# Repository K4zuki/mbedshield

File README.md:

# mbedshield
mbeDshield design and documents

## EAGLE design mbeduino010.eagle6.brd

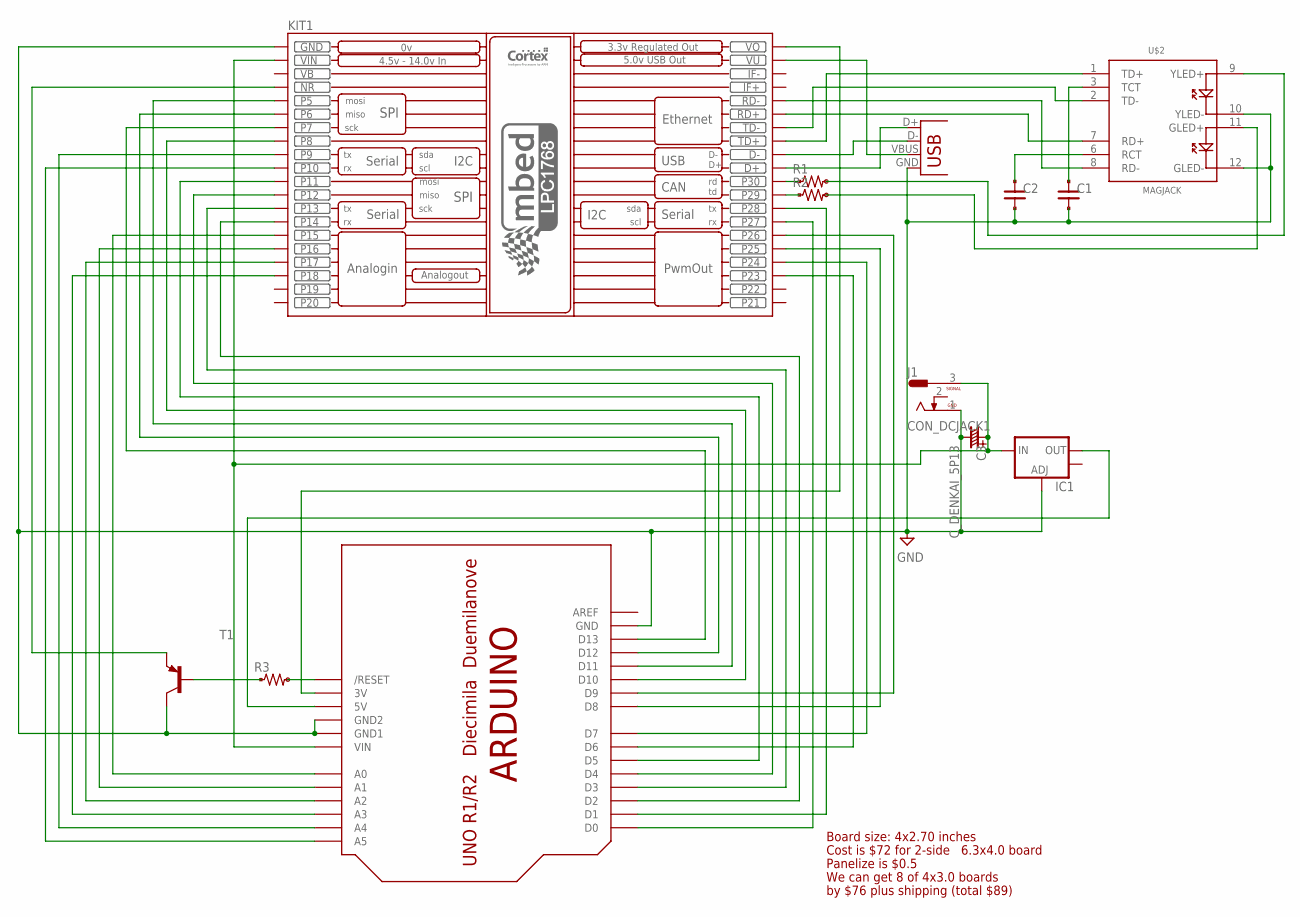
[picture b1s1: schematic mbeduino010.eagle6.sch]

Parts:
C1, C2: C_PAD_PAD_2125; CR_2125
C3: C_DENKAI_5P13; C_2.5PHI6
IC1: V_REG_LM1117SOT223; SOT223
J1: CON_DCJACK1; CON_DCJACK
KIT1: MBED_NXP_LPC1768; MBED-KIT
R1, R2, R3: R_US_PAD_VIA_2125; R_2125_PADVIA
T1: -PNP-SOT23-BCE; SOT23-BCE
U$1: ARDUINO-NOHOLE
U$2: MAGJACK
X1: USB-A-S

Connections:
GND: C1.2, C2.2, C3.-, IC1.1 (ADJ), J1.1 (3), KIT1.GND, T1.C, U$1.GND, U$1.GND1, U$1.GND2, U$2.10 (YLED-), U$2.12 (GLED-), X1.GND
unnamed: KIT1.NR, T1.E
unnamed: C3.+, IC1.3 (IN), J1.3 (1), KIT1.VIN, U$1.VIN
unnamed: KIT1.VOUT (VO), U$1.3V
unnamed: KIT1.P$15 (P15), U$1.A0
unnamed: KIT1.P$16 (P16), U$1.A1
unnamed: KIT1.P$17 (P17), U$1.A2
unnamed: KIT1.P$18 (P18), U$1.A3
unnamed: KIT1.P$9 (P9), U$1.A4
unnamed: KIT1.P$10 (P10), U$1.A5
unnamed: KIT1.P$27 (P27), U$1.D0
unnamed: KIT1.P$28 (P28), U$1.D1
unnamed: KIT1.P$14 (P14), U$1.D2
unnamed: KIT1.P$13 (P13), U$1.D3
unnamed: KIT1.P$12 (P12), U$1.D4
unnamed: KIT1.P$11 (P11), U$1.D5
unnamed: KIT1.P$23 (P23), U$1.D6
unnamed: KIT1.P$24 (P24), U$1.D7
unnamed: KIT1.P$25 (P25), U$1.D8
unnamed: KIT1.P$26 (P26), U$1.D9
unnamed: KIT1.P$8 (P8), U$1.D10
unnamed: KIT1.P$5 (P5), U$1.D11
unnamed: KIT1.P$6 (P6), U$1.D12
unnamed: KIT1.P$7 (P7), U$1.D13
unnamed: KIT1.D-, X1.D-
unnamed: KIT1.D+, X1.D+
unnamed: KIT1.VU, X1.VBUS
unnamed: R3.PAD, T1.B
unnamed: R3.VIA, U$1.RESET (/RESET)
unnamed: C1.1, U$2.3 (TCT)
unnamed: C2.1, U$2.6 (RCT)
unnamed: KIT1.RD+, U$2.7 (RD+)
unnamed: KIT1.RD-, U$2.8 (RD-)
unnamed: KIT1.TD-, U$2.2 (TD-)
unnamed: KIT1.TD+, U$2.1 (TD+)
unnamed: IC1.2 (OUT), U$1.5V
unnamed: KIT1.P$30 (P30), R1.PAD
unnamed: KIT1.P$29 (P29), R2.PAD
unnamed: R1.VIA, U$2.9 (YLED+)
unnamed: R2.VIA, U$2.11 (GLED+)
VB: KIT1.VB

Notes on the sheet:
Board size: 4x2.70 inches
Cost is $72 for 2-side
6.3x4.0 board
Panelize is $0.5
We can get 8 of 4x3.0 boards
by $76 plus shipping (total $89)

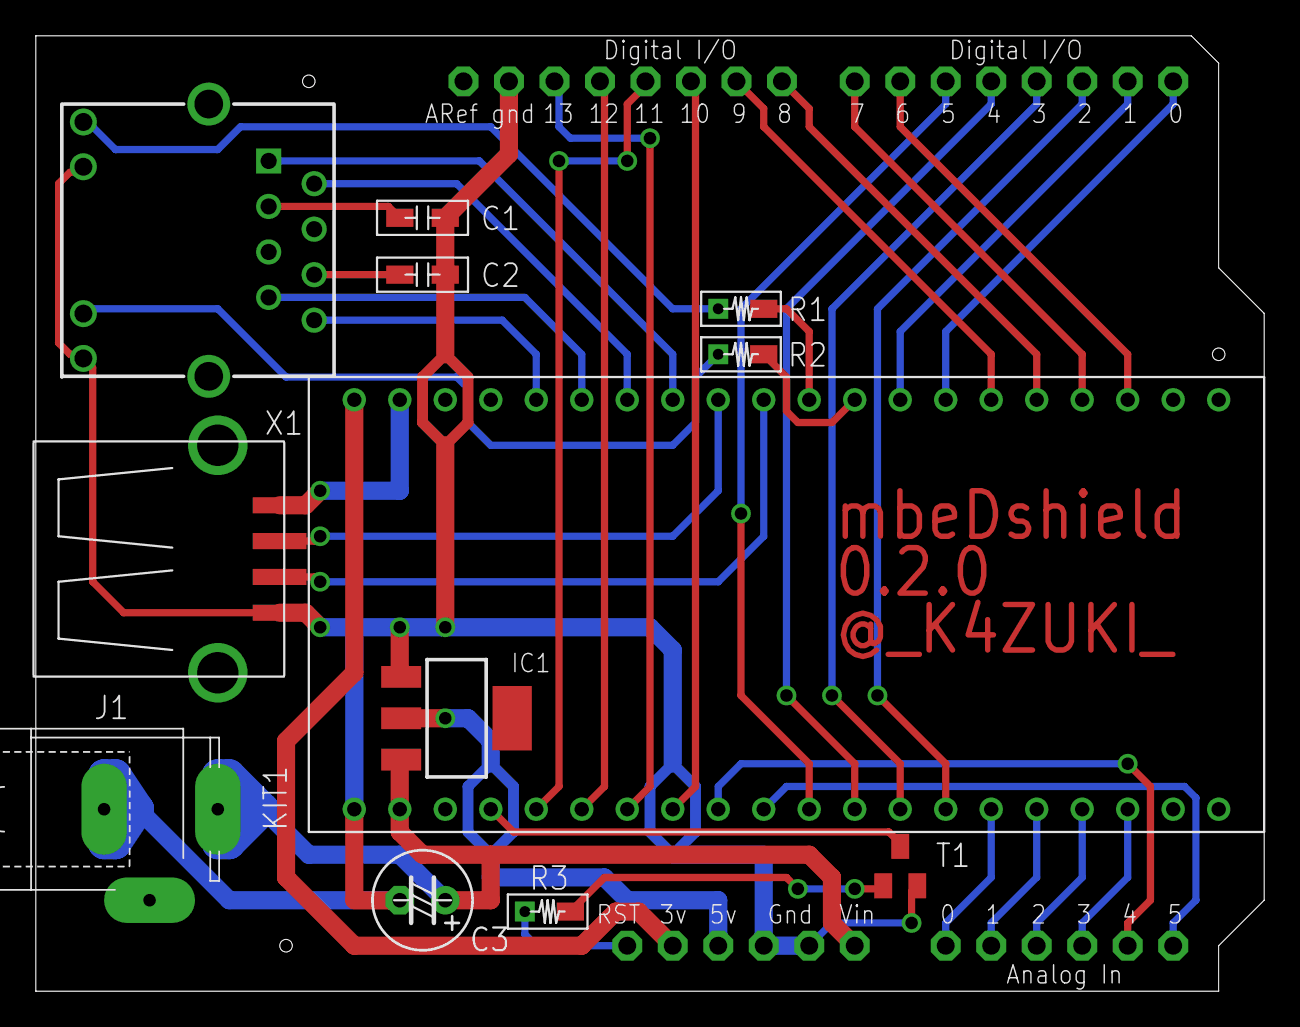
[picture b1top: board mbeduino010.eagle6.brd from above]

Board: 2 copper layers, 68.6 x 53.3 mm, 13 parts (0 on the bottom side), 40 nets.

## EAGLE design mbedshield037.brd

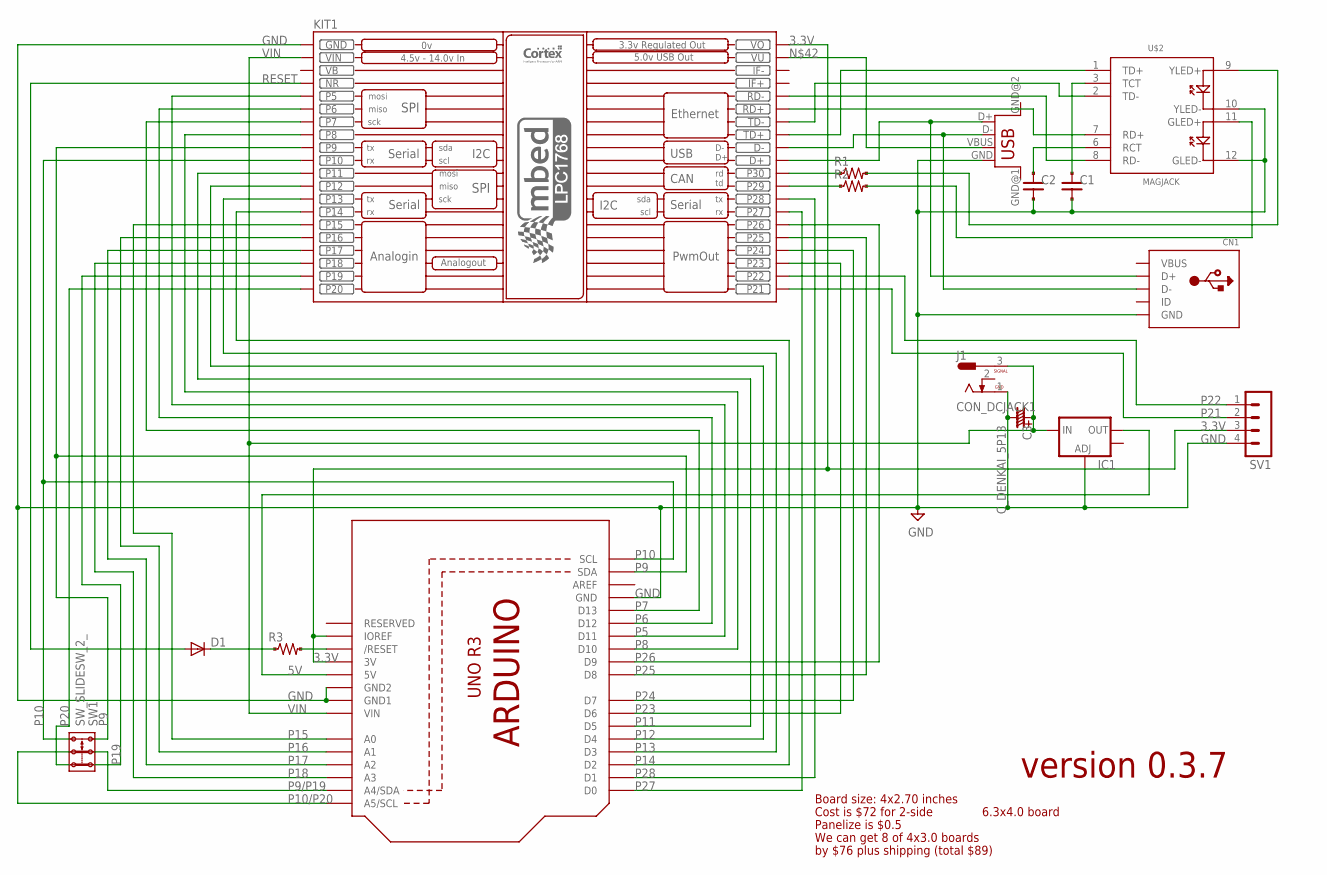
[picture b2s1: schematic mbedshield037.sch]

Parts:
C1, C2: C_PAD_PAD_2125; CR_2125
C3: C_DENKAI_5P13; C_2.5PHI6
CN1: USBMINIB; USB-MINIB
D1: DIODE_SMALL_FLAT_2V; DIODE_2125_2VIA
IC1: V_REG_LM1117SOT223; SOT223
J1: CON_DCJACK1; CON_DCJACK
KIT1: MBED_NXP_LPC1768; MBED-KIT
R1, R2, R3: R_US_PAD_PAD_1608; R_1608_PADPAD
SV1: MA04-1
SW1: SW_SLIDESW_2_; SW_SLIDE_2X2_1
U1: ARDUINOR3-DIMENSION; ARDUINOR3
U$2: MAGJACK
USB: USB; USB-FEMALE-A-PTH

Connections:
3.3V: KIT1.VOUT (VO), SV1.3, U1.3V, U1.IOREF
5V: IC1.2 (OUT), U1.5V
GND: C1.2, C2.2, C3.-, CN1.GND, IC1.1 (ADJ), J1.1 (3), KIT1.GND, SV1.4, U1.GND, U1.GND1, U1.GND2, U$2.10 (YLED-), U$2.12 (GLED-), USB.GND
unnamed: D1.K (C), R3.1
unnamed: R3.2, U1.RESET (/RESET)
unnamed: C1.1, U$2.3 (TCT)
unnamed: C2.1, U$2.6 (RCT)
unnamed: KIT1.RD+, U$2.7 (RD+)
unnamed: KIT1.RD-, U$2.8 (RD-)
unnamed: KIT1.TD-, U$2.2 (TD-)
unnamed: KIT1.TD+, U$2.1 (TD+)
unnamed: KIT1.P$30 (P30), R1.1
unnamed: KIT1.P$29 (P29), R2.1
unnamed: R1.2, U$2.9 (YLED+)
unnamed: R2.2, U$2.11 (GLED+)
unnamed: KIT1.VU, USB.VBUS
unnamed: CN1.D-, KIT1.D-, USB.D-
unnamed: CN1.D+, KIT1.D+, USB.D+
P5: KIT1.P$5 (P5), U1.D11
P6: KIT1.P$6 (P6), U1.D12
P7: KIT1.P$7 (P7), U1.D13
P8: KIT1.P$8 (P8), U1.D10
P9: KIT1.P$9 (P9), SW1.2.1, U1.SDA
P9/P19: SW1.COM.1, U1.A4 (A4/SDA)
P10: KIT1.P$10 (P10), SW1.2.2, U1.SCL
P10/P20: SW1.COM.2, U1.A5 (A5/SCL)
P11: KIT1.P$11 (P11), U1.D5
P12: KIT1.P$12 (P12), U1.D4
P13: KIT1.P$13 (P13), U1.D3
P14: KIT1.P$14 (P14), U1.D2
P15: KIT1.P$15 (P15), U1.A0
P16: KIT1.P$16 (P16), U1.A1
P17: KIT1.P$17 (P17), U1.A2
P18: KIT1.P$18 (P18), U1.A3
P19: KIT1.P$19 (P19), SW1.1.1
P20: KIT1.P$20 (P20), SW1.1.2
P21: KIT1.P$21 (P21), SV1.2
P22: KIT1.P$22 (P22), SV1.1
P23: KIT1.P$23 (P23), U1.D6
P24: KIT1.P$24 (P24), U1.D7
P25: KIT1.P$25 (P25), U1.D8
P26: KIT1.P$26 (P26), U1.D9
P27: KIT1.P$27 (P27), U1.D0
P28: KIT1.P$28 (P28), U1.D1
RESET: D1.A, KIT1.NR
VB: KIT1.VB
VBUS: CN1.VBUS
VIN: C3.+, IC1.3 (IN), J1.3 (1), KIT1.VIN, U1.VIN

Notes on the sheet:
Board size: 4x2.70 inches
Cost is $72 for 2-side
6.3x4.0 board
Panelize is $0.5
We can get 8 of 4x3.0 boards
by $76 plus shipping (total $89)
version 0.3.7

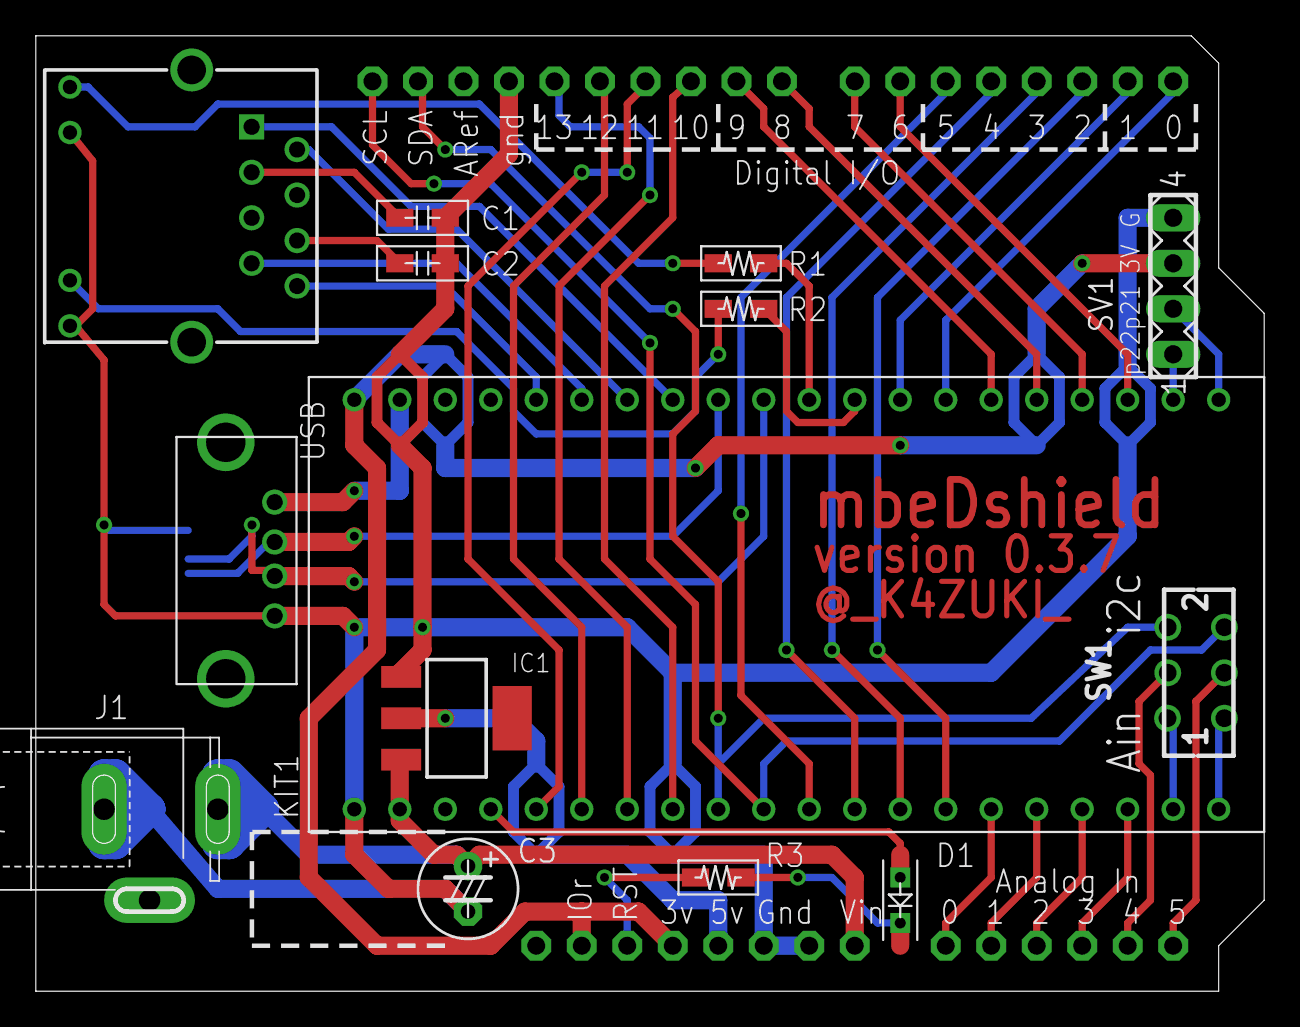
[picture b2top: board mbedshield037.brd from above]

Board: 2 copper layers, 68.3 x 53.1 mm, 16 parts (1 on the bottom side), 46 nets.

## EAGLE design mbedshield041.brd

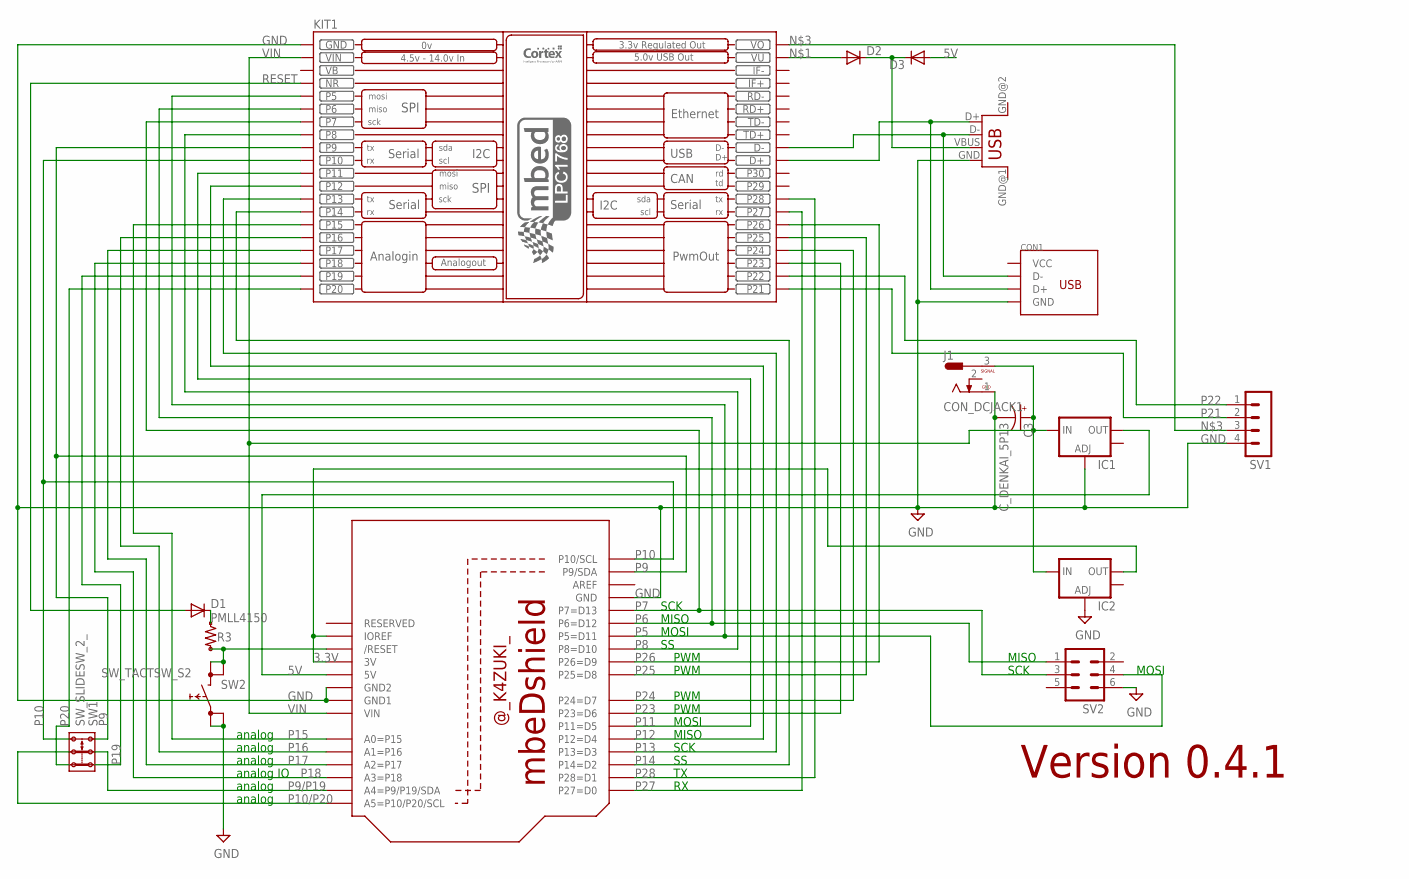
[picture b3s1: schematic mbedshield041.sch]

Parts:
C3: C_DENKAI_5P13; 153CLV-1014
CON1: CON_USB; CON_USB_MINIB_AKI
D1, D2, D3: PMLL4150; SOD80C
IC1, IC2: V_REG_LM1117SOT223; SOT223
J1: CON_DCJACK1; CON_DCJACK
KIT1: MBED_NXP_LPC1768; MBED-KIT
R3: R_US_PAD_VIA_2125; R_2125_PADVIA
SV1: MA04-1
SV2: MA03-2
SW1: SW_SLIDESW_2_; SW_SLIDE_2X2_1
SW2: SW_TACTSW_S2; SW_TACTSW_B3F-10XX
U$1: BOARD_MBEDSHIELD; BOARD_MBEDSHIOELD
USB: USB; USB-FEMALE-A-PTH

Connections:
3.3V: IC2.2 (OUT), U$1.3V, U$1.IOREF
5V: D3.A, IC1.2 (OUT), U$1.5V
GND: C3.-, CON1.GND, IC1.1 (ADJ), IC2.1 (ADJ), J1.1 (3), KIT1.GND, SV1.4, SV2.6, SW2.1 (0), SW2.2 (0), U$1.GND, U$1.GND1, U$1.GND2, USB.GND
unnamed: D2.A, KIT1.VU
unnamed: KIT1.VOUT (VO), SV1.3
unnamed: D1.C, R3.PAD
unnamed: R3.VIA, SW2.3 (1), SW2.4 (1), U$1.RESET (/RESET)
unnamed: D2.C, D3.C, USB.VBUS
unnamed: CON1.D-, KIT1.D-, USB.D-
unnamed: CON1.D+, KIT1.D+, USB.D+
P5: KIT1.P$5 (P5), SV2.4, U$1.D11 (P5=D11)
P6: KIT1.P$6 (P6), SV2.1, U$1.D12 (P6=D12)
P7: KIT1.P$7 (P7), SV2.3, U$1.D13 (P7=D13)
P8: KIT1.P$8 (P8), U$1.D10 (P8=D10)
P9: KIT1.P$9 (P9), SW1.2.1, U$1.SDA (P9/SDA)
P9/P19: SW1.COM.1, U$1.A4 (A4=P9/P19/SDA)
P10: KIT1.P$10 (P10), SW1.2.2, U$1.SCL (P10/SCL)
P10/P20: SW1.COM.2, U$1.A5 (A5=P10/P20/SCL)
P11: KIT1.P$11 (P11), U$1.D5 (P11=D5)
P12: KIT1.P$12 (P12), U$1.D4 (P12=D4)
P13: KIT1.P$13 (P13), U$1.D3 (P13=D3)
P14: KIT1.P$14 (P14), U$1.D2 (P14=D2)
P15: KIT1.P$15 (P15), U$1.A0 (A0=P15)
P16: KIT1.P$16 (P16), U$1.A1 (A1=P16)
P17: KIT1.P$17 (P17), U$1.A2 (A2=P17)
P18: KIT1.P$18 (P18), U$1.A3 (A3=P18)
P19: KIT1.P$19 (P19), SW1.1.1
P20: KIT1.P$20 (P20), SW1.1.2
P21: KIT1.P$21 (P21), SV1.2
P22: KIT1.P$22 (P22), SV1.1
P23: KIT1.P$23 (P23), U$1.D6 (P23=D6)
P24: KIT1.P$24 (P24), U$1.D7 (P24=D7)
P25: KIT1.P$25 (P25), U$1.D8 (P25=D8)
P26: KIT1.P$26 (P26), U$1.D9 (P26=D9)
P27: KIT1.P$27 (P27), U$1.D0 (P27=D0)
P28: KIT1.P$28 (P28), U$1.D1 (P28=D1)
RESET: D1.A, KIT1.NR
VB: KIT1.VB
VIN: C3.+, IC1.3 (IN), IC2.3 (IN), J1.3 (1), KIT1.VIN, U$1.VIN

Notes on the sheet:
MOSI
MISO
SCK
PWM
analog
analog IO
Version 0.4.1

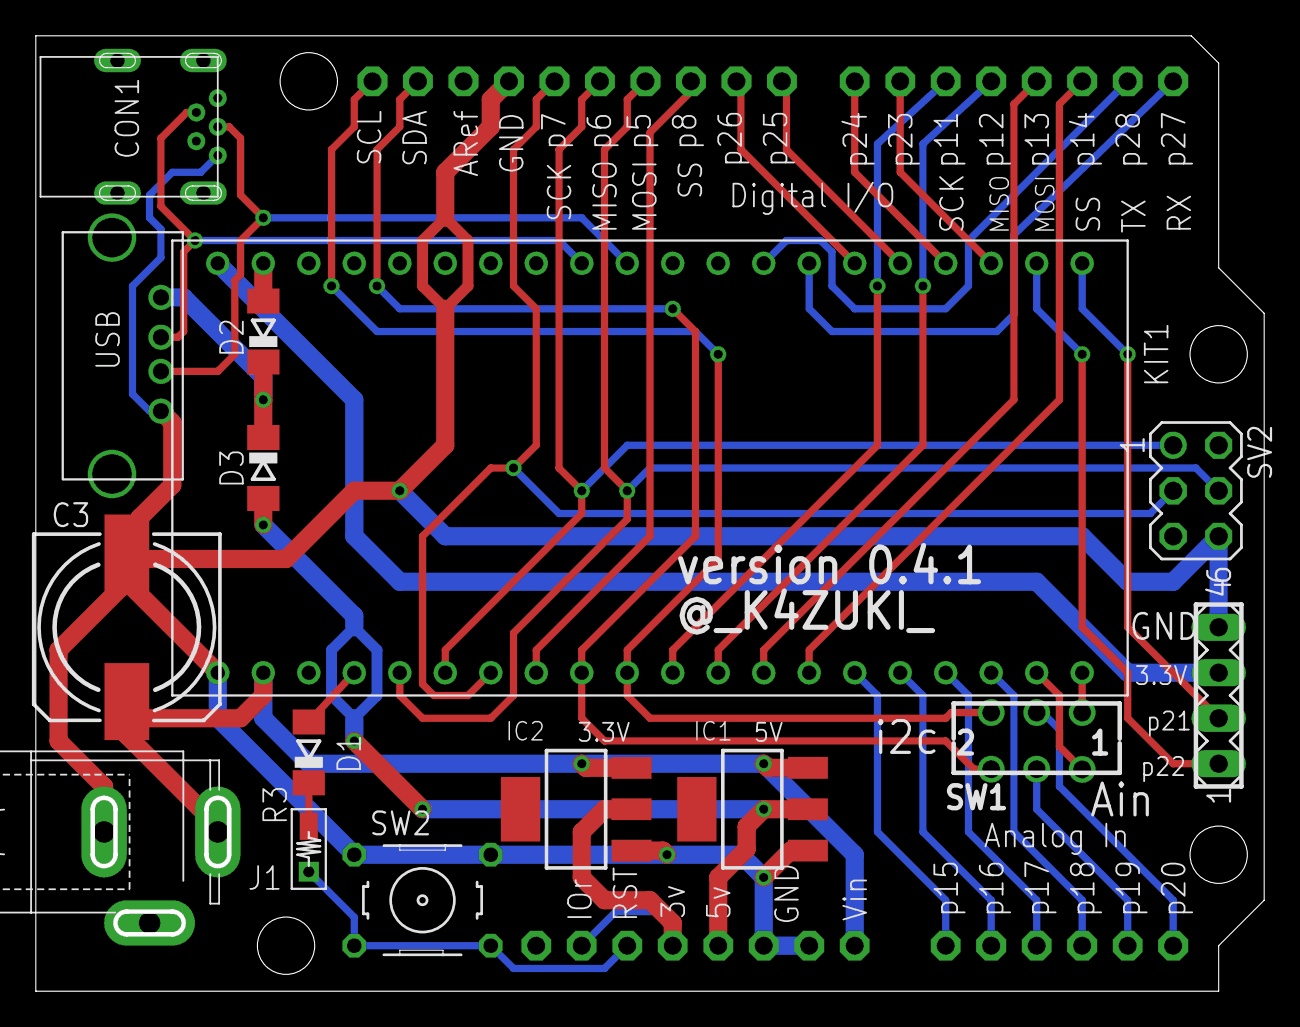
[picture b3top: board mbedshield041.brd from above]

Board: 2 copper layers, 68.3 x 53.1 mm, 16 parts (0 on the bottom side), 38 nets.

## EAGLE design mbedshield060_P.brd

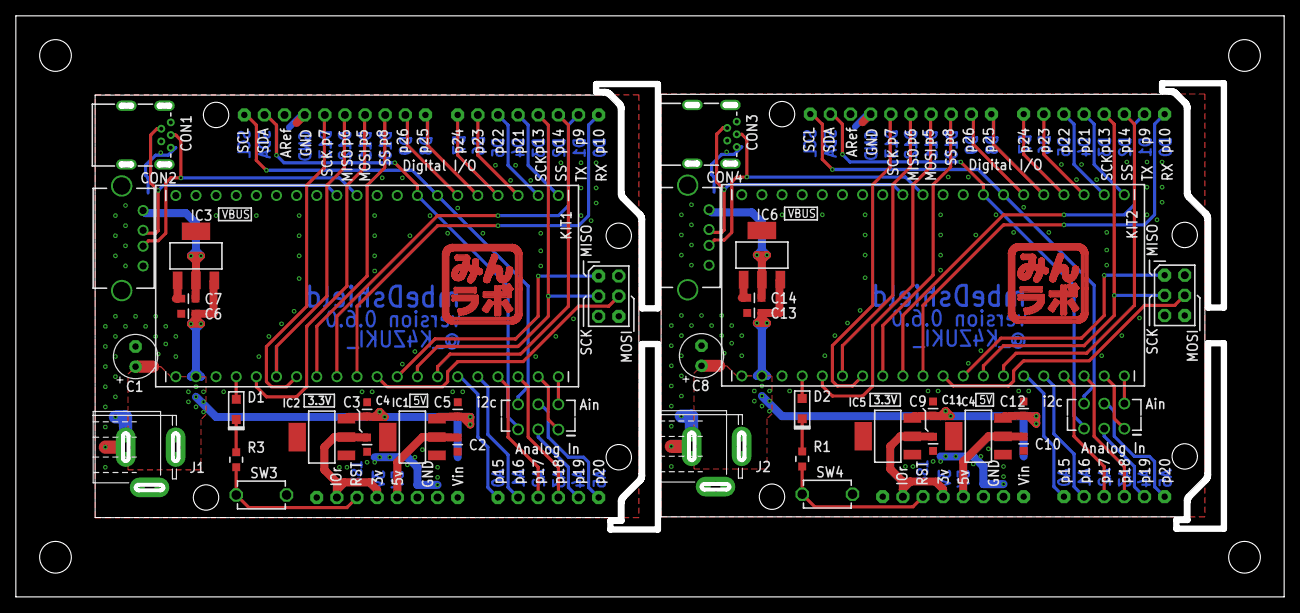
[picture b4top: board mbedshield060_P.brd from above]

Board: 2 copper layers, 159.2 x 72.5 mm, 40 parts (0 on the bottom side), 72 nets.

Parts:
C1, C8: P-5002; C_2.5PHI6
C2, C3, C4, C5, C6, C7, C9, C10, C11, C12, C13, C14: CR_1608
CON1, CON3: C-2235; CON_USB_MINIB_AKI
CON2, CON4: CON_USB_A_SHIELD
D1, D2: I-2073; DIODE_2125
I1, I2: ICON_MINLAB_M2; ICON_MINLAB_2
IC1, IC3, IC4, IC6: I-2503; SOT223
IC2, IC5: I-2502; SOT223
J1, J2: C-6568; CON_DCJACK
KIT1, KIT2: MBED_NXP_LPC1768; MBED-KIT
R1, R3: R_1608_PADPAD
SW1, SW2: P-2627; SW_SLIDE_2X2_1
SW3, SW4: SW_TACTSW_2PP8073; SW_TACTSW_P8073
U$1, U$2: mbeDshield060; BOARD_MBEDSHIELD3

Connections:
3.3V: C3.1, IC2.2, U$1.3V, U$1.IOREF
3.3V1: C9.1, IC5.2, U$2.3V, U$2.IOREF
5V: C2.1, IC1.2, U$1.5V
5V1: C10.1, IC4.2, U$2.5V
GND: C1.-, C2.2, C3.2, C4.2, C5.2, C6.2, C7.2, CON1.GND, CON1.GND@1, CON1.GND@2, CON1.GND@3, CON1.GND@4, CON2.4, IC1.1, IC2.1, IC3.1, J1.1, KIT1.GND, SW3.A1, U$1.GND, U$1.GND1, U$1.GND2, U$1.GND3
GND1: C8.-, C9.2, C10.2, C11.2, C12.2, C13.2, C14.2, CON3.GND, CON3.GND@1, CON3.GND@2, CON3.GND@3, CON3.GND@4, CON4.4, IC4.1, IC5.1, IC6.1, J2.1, KIT2.GND, SW4.A1, U$2.GND, U$2.GND1, U$2.GND2, U$2.GND3
unnamed: CON1.D-, CON2.2, KIT1.D-
unnamed: R1.2, SW4.A2, U$2.RESET
unnamed: D2.K, R1.1
unnamed: CON3.D+, CON4.3, KIT2.D+
unnamed: CON3.D-, CON4.2, KIT2.D-
unnamed: D1.K, R3.1
unnamed: R3.2, SW3.A2, U$1.RESET
unnamed: CON1.D+, CON2.3, KIT1.D+
P1: KIT2.P$15, U$2.A0
P2: KIT2.P$16, U$2.A1
P3: KIT2.P$17, U$2.A2
P4: KIT2.P$18, U$2.A3
P5: KIT1.P$5, U$1.D11
P6: KIT1.P$6, U$1.D12
P7: KIT1.P$7, U$1.D13
P8: KIT1.P$8, U$1.D10
P9: KIT1.P$9, U$1.D1
P10: KIT1.P$10, U$1.D0
P11: KIT1.P$11, U$1.P11
P12: KIT1.P$12, U$1.P12
P13: KIT1.P$13, U$1.D3, U$1.P13
P14: KIT1.P$14, U$1.D2
P15: KIT1.P$15, U$1.A0
P16: KIT1.P$16, U$1.A1
P17: KIT1.P$17, U$1.A2
P18: KIT1.P$18, U$1.A3
P19: KIT1.P$19, SW1.1.1
P20: KIT1.P$20, SW1.1.2
P21: KIT1.P$21, U$1.D4
P22: KIT1.P$22, U$1.D5
P23: KIT1.P$23, U$1.D6
P24: KIT1.P$24, U$1.D7
P25: KIT1.P$25, U$1.D8
P26: KIT1.P$26, U$1.D9
P27: KIT1.P$27, SW1.2.2, U$1.SCL
P27/P1: SW2.COM.2, U$2.A5
P27/P20: SW1.COM.2, U$1.A5
P28: KIT1.P$28, SW1.2.1, U$1.SDA
P28/P1: SW2.COM.1, U$2.A4
P28/P19: SW1.COM.1, U$1.A4
P29: KIT2.P$9, U$2.D1
P30: KIT2.P$27, SW2.2.2, U$2.SCL
P31: KIT2.P$28, SW2.2.1, U$2.SDA
P32: KIT2.P$14, U$2.D2
P33: KIT2.P$13, U$2.D3, U$2.P13
P34: KIT2.P$12, U$2.P12
P35: KIT2.P$11, U$2.P11
P36: KIT2.P$23, U$2.D6
P37: KIT2.P$24, U$2.D7
P38: KIT2.P$25, U$2.D8
P39: KIT2.P$26, U$2.D9
P40: KIT2.P$8, U$2.D10
P41: KIT2.P$5, U$2.D11
P42: KIT2.P$6, U$2.D12
P43: KIT2.P$7, U$2.D13
P44: KIT2.P$10, U$2.D0
P45: KIT2.P$19, SW2.1.1
P46: KIT2.P$20, SW2.1.2
P47: KIT2.P$22, U$2.D5
P48: KIT2.P$21, U$2.D4
RESET: D1.A, KIT1.NR
RESET1: D2.A, KIT2.NR
VBUS: C7.1, CON2.1, IC3.2
VBUS1: C14.1, CON4.1, IC6.2
VIN: C1.+, C4.1, C5.1, C6.1, IC1.3, IC2.3, IC3.3, J1.3, KIT1.VIN, U$1.VIN
VIN1: C8.+, C11.1, C12.1, C13.1, IC4.3, IC5.3, IC6.3, J2.3, KIT2.VIN, U$2.VIN

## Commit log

2015-12-09 PCB - initial commit
    0.3.7/0.4.0/0.4.1/0.4.2/0.5.0/0.6.0/0.6.0_P
2015-12-09 add pictures
2015-12-09 add documents
2015-12-09 add function diagram
2015-12-09 add 0.5.0 piout
2015-12-09 add other old pics
2015-12-09 rename to prototype.jpg
2015-12-09 rename to mbedshield050.vsd
2015-12-09 add mbedshield050.functioni.png
2015-12-09 rename to instruction_ether.jpg
2015-12-09 rename to instruction_connector.jpg
2015-12-09 add makefiles
2015-12-09 gitignore
2015-12-10 Makefiles update
2015-12-10 add new pics: mbedshield[037/040/041/042].png
2015-12-10 pic pointers update
2015-12-11 update recvision history
2015-12-12 gitignore aux,toc,out,log
2015-12-14 add mbeduino010.png
2015-12-14 add mbeduino010 schematic and layout in eagle6 format
2015-12-14 add 0.6.0 schematic pic (portrait)
2015-12-14 add LaTex template
2015-12-14 ignore .out output
2015-12-26 make pdf disabled by default
2015-12-27 add captions for pictures; add more footnotes; update revision
2016-01-08 mbedShield.md: source file for next revision
2016-01-08 update makefiles
2016-01-09 cleans *.mono.png
2016-01-09 disable making *.mono.png
2016-01-09 some abstract fix; all pics have table title
2016-01-11 change PDF compile option
2016-01-11 clearer template look
2016-01-11 add/update variables; replace table style
2016-01-12 ignores */Thumbs.db
